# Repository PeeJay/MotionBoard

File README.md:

# MotionBoard
FirePick Delta/Ramps compatible motion controller running Smoothie

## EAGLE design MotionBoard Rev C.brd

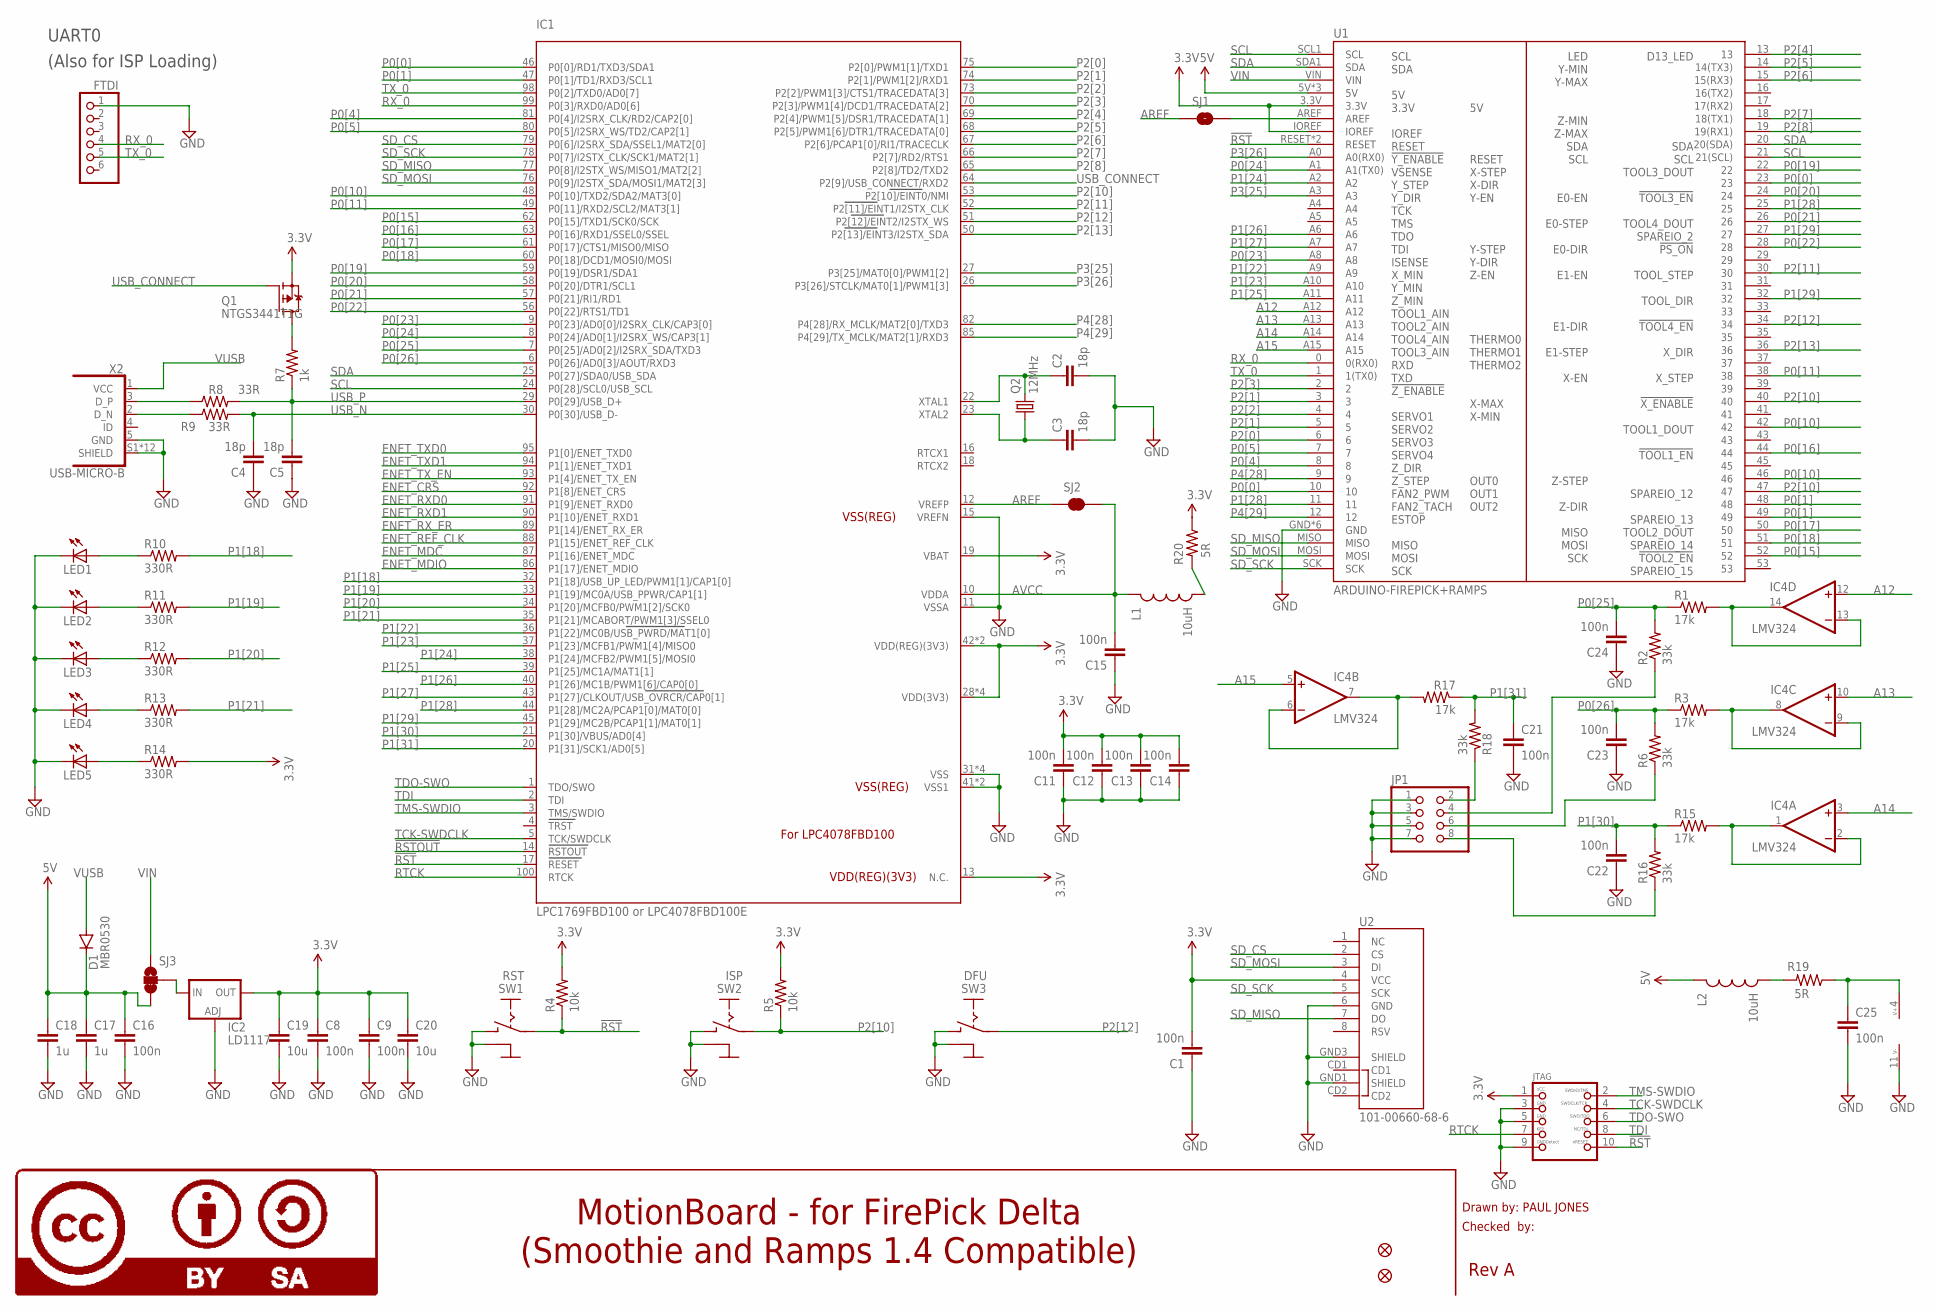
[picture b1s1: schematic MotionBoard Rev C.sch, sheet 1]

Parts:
C1, C8, C9, C11, C12, C13, C14, C15, C16, C21, C22, C23, C24, C25: 100n; 0603
C2, C3, C4, C5: 18p; 0603
C17, C18: 1u; 0603
C19, C20: 10u; 0603
D1: MBR0530; SOD-123
DFU: SW3; TOGGLE-SW-SMD
FID5, FID6: FIDUCIAL1X2; FIDUCIAL-1X2
FTDI: PINHD-1X6; 1X06
IC1: LPC1769FBD100 or LPC4078FBD100E; LQFP100
IC2: LD1117; SOT223
IC4: LMV324; SO14
ISP: SW2; TOGGLE-SW-SMD
JP1: PINHD-2X04_2.54-SMD; 2X04SMD
JTAG: JTAG-CORTEXM3; 2X05_1.27MM_SMT
L1, L2: 10uH; 0603
LED1, LED2, LED3, LED4, LED5: LED; LED-1206-BOTTOM
LOGO6: LOGO-CC-BY-SAMEDIUM; LOGO-CC-BY-SA-MEDIUM
Q1: NTGS3441T1G; SC74_INFINEON
Q2: 12MHz; HC49UP
R1, R3, R15, R17: 17k; 0603
R2, R6, R16, R18: 33k; 0603
R4, R5: 10k; R0603
R7: 1k; R0603
R8, R9: 33R; R0603
R10, R11, R12, R13, R14: 330R; R0603
R19, R20: 5R; 0603
RST: SW1; TOGGLE-SW-SMD
SJ1: JUMPER-PAD-2-NOYES_SILK; PAD-JUMPER-2-NO_YES_SILK
SJ2: JUMPER-PAD-2-NC_BY_TRACE; PAD-JUMPER-2-NC_BY_TRACE_YES_SILK
SJ3: JUMPER-PAD-3-2OF3_NC_BY_TRACE_SMALL; PAD-JUMPER-3-2OF3_NC_BY_TRACE_YES_SILK_FULL_BOX
U1: ARDUINO-FIREPICK+RAMPS; ARDUINO_MEGA_NEW
U2: 101-00660-68-6; MICRO-SD-SOCKET-PP
X2: USB-MICRO-B; FCI-10118194-0001LF

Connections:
3.3V: C1.2, C8.1, C9.1, C11.2, C12.2, C13.2, C14.2, C19.1, C20.1, IC1.13 (N.C.), IC1.19 (VBAT), IC1.28 (VDD(3V3)), IC1.42 (VDD(REG)(3V3)), IC1.54 (VDD(3V3)), IC1.71 (VDD(3V3)), IC1.84 (VDD(REG)(3V3)), IC1.96 (VDD(3V3)), IC2.4 (OUT), JTAG.1, Q1.4 (S), R4.2, R5.2, R14.2, R20.1, U1.3.3V, U1.IOREF, U2.4 (VCC); also elsewhere on the board
5V: C16.1, C17.1, C18.1, D1.C, L2.1, SJ3.3, U1.5V, U1.5V@1 (5V), U1.5V@2 (5V)
!RST: IC1.17 (RESET), JTAG.10, R4.1, RST.3 (I), RST.4 (I), U1.RESET, U1.RST (RESET)
!RSTOUT: IC1.14 (RSTOUT); also elsewhere on the board
A12: IC4.12 (+IN), U1.A12
A13: IC4.10 (+IN), U1.A13
A14: IC4.3 (+IN), U1.A14
A15: IC4.5 (+IN), U1.A15
AREF: IC1.12 (VREFP), SJ1.1, SJ2.1
AVCC: C15.2, IC1.10 (VDDA), L1.1, SJ2.2
D_N: R9.1, X2.2 (D_N)
D_P: R8.1, X2.3 (D_P)
ENET_CRS: IC1.92 (P1[8]/ENET_CRS); also elsewhere on the board
ENET_MDC: IC1.87 (P1[16]/ENET_MDC); also elsewhere on the board
ENET_MDIO: IC1.86 (P1[17]/ENET_MDIO); also elsewhere on the board
ENET_REF_CLK: IC1.88 (P1[15]/ENET_REF_CLK); also elsewhere on the board
ENET_RXD0: IC1.91 (P1[9]/ENET_RXD0); also elsewhere on the board
ENET_RXD1: IC1.90 (P1[10]/ENET_RXD1); also elsewhere on the board
ENET_RX_ER: IC1.89 (P1[14]/ENET_RX_ER); also elsewhere on the board
ENET_TXD0: IC1.95 (P1[0]/ENET_TXD0); also elsewhere on the board
ENET_TXD1: IC1.94 (P1[1]/ENET_TXD1); also elsewhere on the board
ENET_TX_EN: IC1.93 (P1[4]/ENET_TX_EN); also elsewhere on the board
GND: C1.1, C2.2, C3.2, C4.1, C5.1, C8.2, C9.2, C11.1, C12.1, C13.1, C14.1, C15.1, C16.2, C17.2, C18.2, C19.2, C20.2, C21.2, C22.1, C23.1, C24.1, C25.2, DFU.1 (C), DFU.2 (C), DFU.GND, FTDI.1, IC1.11 (VSSA), IC1.15 (VREFN), IC1.31 (VSS), IC1.41 (VSS1), IC1.55 (VSS), IC1.72 (VSS), IC1.83 (VSS1), IC1.97 (VSS), IC2.1 (ADJ), IC4.11 (V-), ISP.1 (C), ISP.2 (C), ISP.GND, JP1.1, JP1.3, JP1.5, JP1.7, JTAG.3, JTAG.5, JTAG.9, LED1.C, LED2.C, LED3.C, LED4.C, LED5.C, RST.1 (C), RST.2 (C), RST.GND, U1.GND, U1.GND@0 (GND), U1.GND@1 (GND), U1.GND@2 (GND), U1.GND@3 (GND), U1.GNDI (GND), U2.6 (GND), U2.GND1 (SHIELD), U2.GND3 (SHIELD), X2.5 (GND), X2.S1 (SHIELD), X2.S2 (SHIELD), X2.S3 (SHIELD), X2.S4 (SHIELD), X2.S5 (SHIELD), X2.S6 (SHIELD), X2.S7 (SHIELD), X2.S8 (SHIELD), X2.S9 (SHIELD), X2.S10 (SHIELD), X2.S11 (SHIELD), X2.S12 (SHIELD); also elsewhere on the board
unnamed: C2.1, IC1.22 (XTAL1), Q2.2
unnamed: C3.1, IC1.23 (XTAL2), Q2.1
unnamed: SJ1.2, U1.AREF
unnamed: IC4.6 (-IN), IC4.7 (OUT), R17.2
unnamed: IC2.3 (IN), SJ3.2
unnamed: JP1.2, R18.1
unnamed: IC4.13 (-IN), IC4.14 (OUT), R1.2
unnamed: JP1.8, R16.1
unnamed: IC4.8 (OUT), IC4.9 (-IN), R3.2
unnamed: JP1.6, R6.1
unnamed: IC4.1 (OUT), IC4.2 (-IN), R15.2
unnamed: JP1.4, R2.1
unnamed: C25.1, IC4.4 (V+), R19.1
unnamed: L2.2, R19.2
unnamed: L1.2, R20.2
unnamed: Q1.1 (D), Q1.2 (D), Q1.5 (D), Q1.6 (D), R7.2
unnamed: LED5.A, R14.1
unnamed: LED4.A, R13.1
unnamed: LED3.A, R12.1
unnamed: LED2.A, R11.1
unnamed: LED1.A, R10.1
P0[0]: IC1.46 (P0[0]/RD1/TXD3/SDA1), U1.10, U1.23
P0[1]: IC1.47 (P0[1]/TD1/RXD3/SCL1), U1.48, U1.49
P0[4]: IC1.81 (P0[4]/I2SRX_CLK/RD2/CAP2[0]), U1.8
P0[5]: IC1.80 (P0[5]/I2SRX_WS/TD2/CAP2[1]), U1.7
P0[10]: IC1.48 (P0[10]/TXD2/SDA2/MAT3[0]), U1.42, U1.46
P0[11]: IC1.49 (P0[11]/RXD2/SCL2/MAT3[1]), U1.38
P0[15]: IC1.62 (P0[15]/TXD1/SCK0/SCK), U1.52
P0[16]: IC1.63 (P0[16]/RXD1/SSEL0/SSEL), U1.44
P0[17]: IC1.61 (P0[17]/CTS1/MISO0/MISO), U1.50
P0[18]: IC1.60 (P0[18]/DCD1/MOSI0/MOSI), U1.51
P0[19]: IC1.59 (P0[19]/DSR1/SDA1), U1.22
P0[20]: IC1.58 (P0[20]/DTR1/SCL1), U1.24
P0[21]: IC1.57 (P0[21]/RI1/RD1), U1.26
P0[22]: IC1.56 (P0[22]/RTS1/TD1), U1.28
P0[23]: IC1.9 (P0[23]/AD0[0]/I2SRX_CLK/CAP3[0]), U1.A8
P0[24]: IC1.8 (P0[24]/AD0[1]/I2SRX_WS/CAP3[1]), U1.A1 (A1(TX0))
P0[25]: C24.2, IC1.7 (P0[25]/AD0[2]/I2SRX_SDA/TXD3), R1.1, R2.2
P0[26]: C23.2, IC1.6 (P0[26]/AD0[3]/AOUT/RXD3), R3.1, R6.2
P1[18]: IC1.32 (P1[18]/USB_UP_LED/PWM1[1]/CAP1[0]), R10.2
P1[19]: IC1.33 (P1[19]/MC0A/USB_PPWR/CAP1[1]), R11.2
P1[20]: IC1.34 (P1[20]/MCFB0/PWM1[2]/SCK0), R12.2
P1[21]: IC1.35 (P1[21]/MCABORT/PWM1[3]/SSEL0), R13.2
P1[22]: IC1.36 (P1[22]/MC0B/USB_PWRD/MAT1[0]), U1.A9
P1[23]: IC1.37 (P1[23]/MCFB1/PWM1[4]/MISO0), U1.A10
P1[24]: IC1.38 (P1[24]/MCFB2/PWM1[5]/MOSI0), U1.A2
P1[25]: IC1.39 (P1[25]/MC1A/MAT1[1]), U1.A11
P1[26]: IC1.40 (P1[26]/MC1B/PWM1[6]/CAP0[0]), U1.A6
P1[27]: IC1.43 (P1[27]/CLKOUT/USB_OVRCR/CAP0[1]), U1.A7
P1[28]: IC1.44 (P1[28]/MC2A/PCAP1[0]/MAT0[0]), U1.11, U1.25
P1[29]: IC1.45 (P1[29]/MC2B/PCAP1[1]/MAT0[1]), U1.27, U1.32
P1[30]: C22.2, IC1.21 (P1[30]/VBUS/AD0[4]), R15.1, R16.2
P1[31]: C21.1, IC1.20 (P1[31]/SCK1/AD0[5]), R17.1, R18.2
P2[0]: IC1.75 (P2[0]/PWM1[1]/TXD1), U1.6
P2[1]: IC1.74 (P2[1]/PWM1[2]/RXD1), U1.3, U1.5
P2[2]: IC1.73 (P2[2]/PWM1[3]/CTS1/TRACEDATA[3]), U1.4
P2[3]: IC1.70 (P2[3]/PWM1[4]/DCD1/TRACEDATA[2]), U1.2
P2[4]: IC1.69 (P2[4]/PWM1[5]/DSR1/TRACEDATA[1]), U1.13
P2[5]: IC1.68 (P2[5]/PWM1[6]/DTR1/TRACEDATA[0]), U1.14 (14(TX3))
P2[6]: IC1.67 (P2[6]/PCAP1[0]/RI1/TRACECLK), U1.15 (15(RX3))
P2[7]: IC1.66 (P2[7]/RD2/RTS1), U1.18 (18(TX1))
P2[8]: IC1.65 (P2[8]/TD2/TXD2), U1.19 (19(RX1))
P2[10]: IC1.53 (P2[10]/EINT0/NMI), ISP.3 (I), ISP.4 (I), R5.1, U1.40, U1.47
P2[11]: IC1.52 (P2[11]/EINT1/I2STX_CLK), U1.30
P2[12]: DFU.3 (I), DFU.4 (I), IC1.51 (P2[12]/EINT2/I2STX_WS), U1.34
P2[13]: IC1.50 (P2[13]/EINT3/I2STX_SDA), U1.36
P3[25]: IC1.27 (P3[25]/MAT0[0]/PWM1[2]), U1.A3
P3[26]: IC1.26 (P3[26]/STCLK/MAT0[1]/PWM1[3]), U1.A0 (A0(RX0))
P4[28]: IC1.82 (P4[28]/RX_MCLK/MAT2[0]/TXD3), U1.9
P4[29]: IC1.85 (P4[29]/TX_MCLK/MAT2[1]/RXD3), U1.12
RTCK: IC1.100 (RTCK), JTAG.7
RX_0: FTDI.4, IC1.99 (P0[3]/RXD0/AD0[6]), U1.0 (0(RX0))
SCL: IC1.24 (P0[28]/SCL0/USB_SCL), U1.21 (21(SCL)), U1.SCL1 (SCL)
SDA: IC1.25 (P0[27]/SDA0/USB_SDA), U1.20 (20(SDA)), U1.SDA1 (SDA)
SD_CS: IC1.79 (P0[6]/I2SRX_SDA/SSEL1/MAT2[0]), U2.2 (CS)
SD_MISO: IC1.77 (P0[8]/I2STX_WS/MISO1/MAT2[2]), U1.MISO, U2.7 (DO)
SD_MOSI: IC1.76 (P0[9]/I2STX_SDA/MOSI1/MAT2[3]), U1.MOSI, U2.3 (DI)
SD_SCK: IC1.78 (P0[7]/I2STX_CLK/SCK1/MAT2[1]), U1.SCK, U2.5 (SCK)
TCK-SWDCLK: IC1.5 (TCK/SWDCLK), JTAG.4
TDI: IC1.2 (TDI), JTAG.8
TDO-SWO: IC1.1 (TDO/SWO), JTAG.6
TMS-SWDIO: IC1.3 (TMS/SWDIO), JTAG.2
TX_0: FTDI.5, IC1.98 (P0[2]/TXD0/AD0[7]), U1.1 (1(TX0))
USB_CONNECT: IC1.64 (P2[9]/USB_CONNECT/RXD2), Q1.3 (G)
USB_N: C4.2, IC1.30 (P0[30]/USB_D-), R9.2
USB_P: C5.2, IC1.29 (P0[29]/USB_D+), R7.1, R8.2
VIN: SJ3.1, U1.VIN
VUSB: D1.A, X2.1 (VCC)

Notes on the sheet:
Drawn by: PAUL JONES
Checked by:
Rev A
MotionBoard - for FirePick Delta (Smoothie and Ramps 1.4 Compatible)
UART0
(Also for ISP Loading)

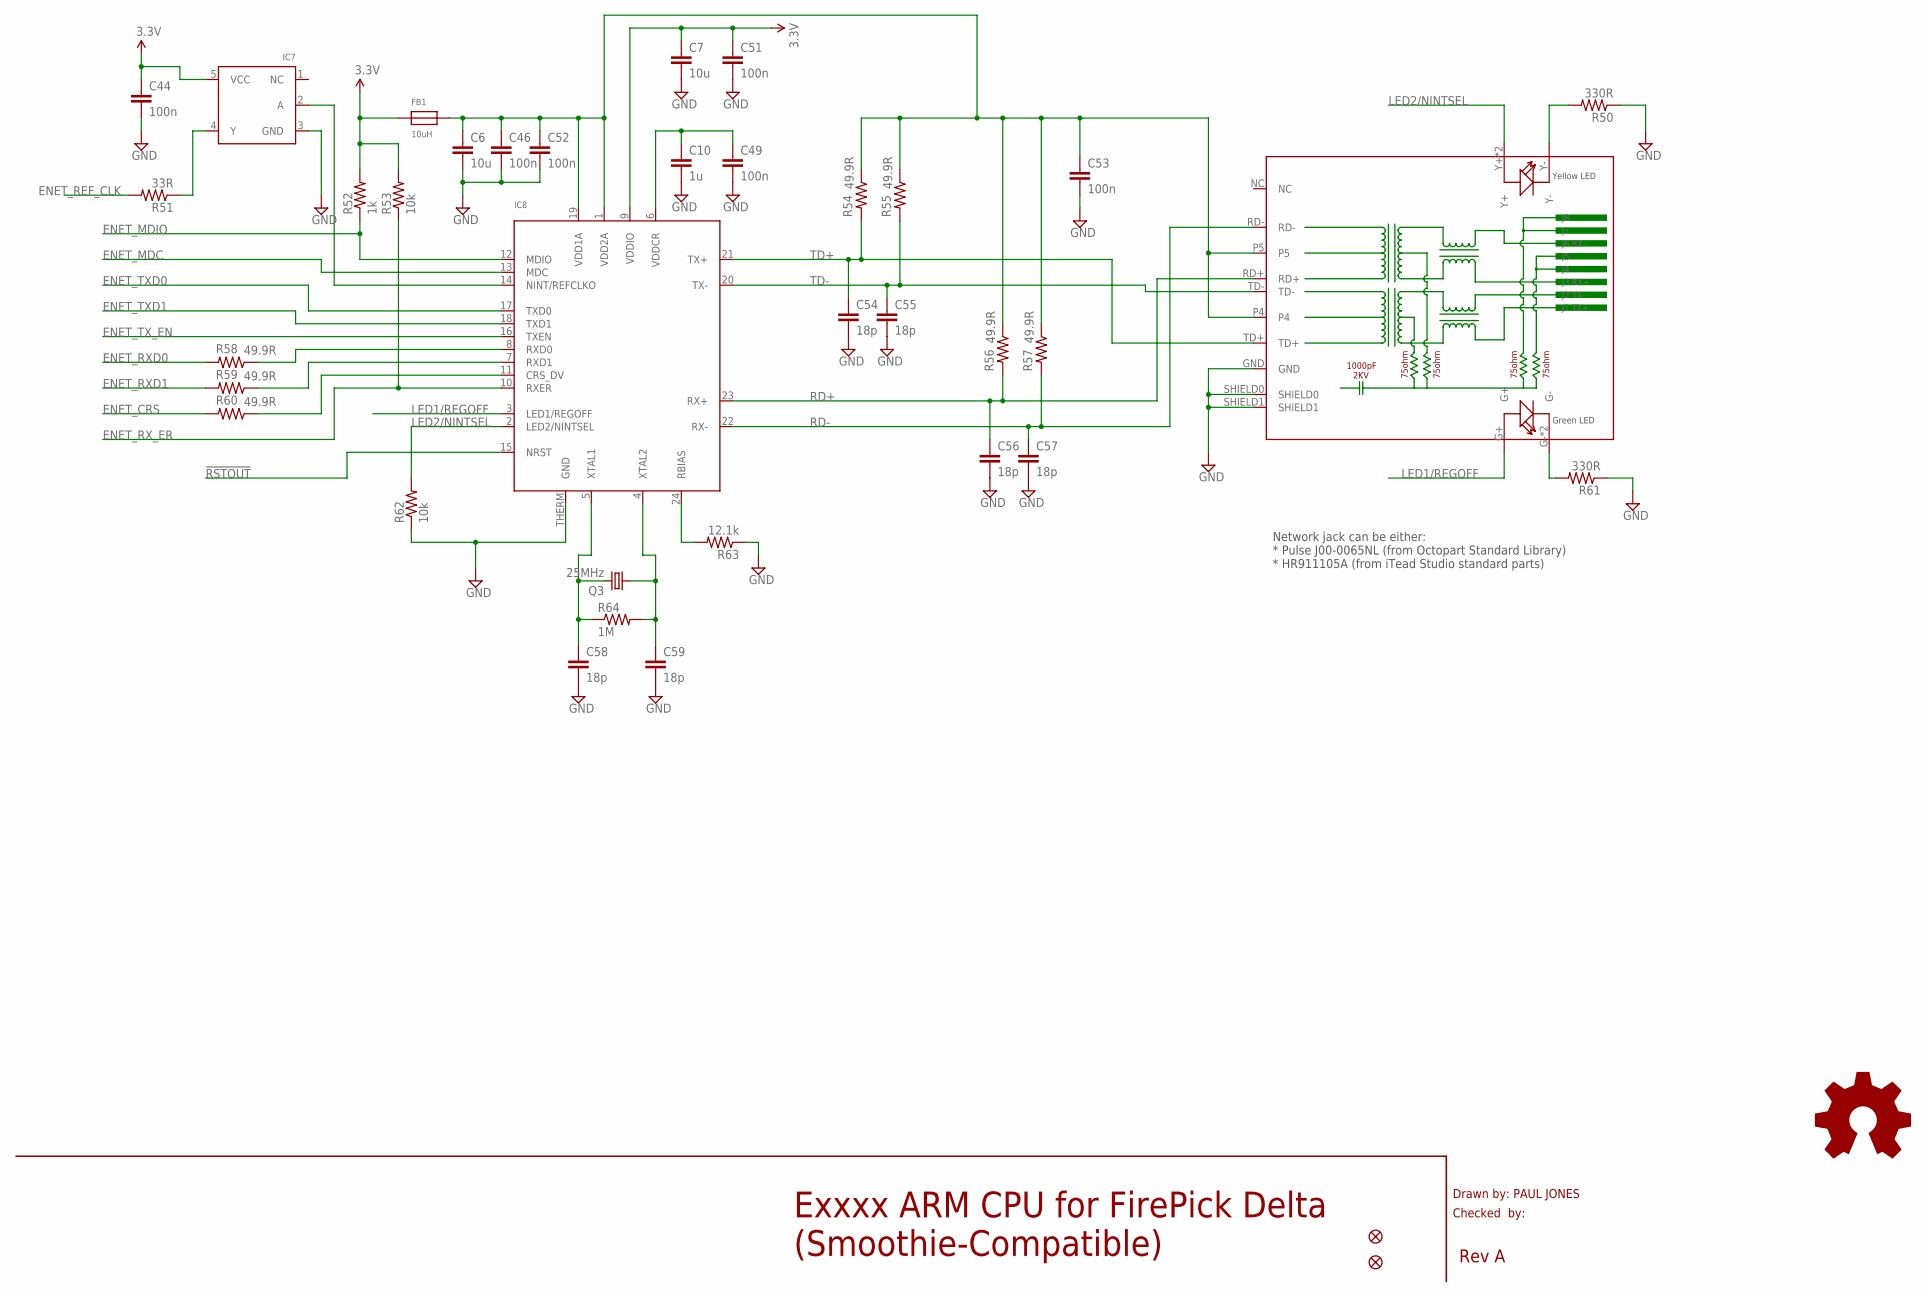
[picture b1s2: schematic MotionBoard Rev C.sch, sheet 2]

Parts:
C6, C7: 10u; 0603
C10: 1u; 0603
C44, C46, C49, C51, C52, C53: 100n; 0603
C54, C55, C56, C57, C58, C59: 18p; 0603
FB1: 10uH; 0603
FID17, FID18: FIDUCIAL1X2; FIDUCIAL-1X2
IC7: 74LVC1G04; SOT23-5
IC8: LAN8720; QFN24_4MM
LOGO10: LOGO-OSHWSMALL; LOGO-OSHW-SMALL
Q3: 25MHz; HC49UP
R50, R61: 330R; R0603
R51: 33R; R0603
R52: 1k; R0603
R53, R62: 10k; R0603
R54, R55, R56, R57, R58, R59, R60: 49.9R; R0603
R63: 12.1k; R0603
R64: 1M; R0603
RJ1: HR911105A

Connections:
3.3V: C7.1, C44.1, C51.1, FB1.1, IC7.5 (VCC), IC8.9 (VDDIO), R52.2, R53.2; also elsewhere on the board
!RSTOUT: IC8.15 (NRST); also elsewhere on the board
ENET_CRS: R60.2; also elsewhere on the board
ENET_MDC: IC8.13 (MDC); also elsewhere on the board
ENET_MDIO: IC8.12 (MDIO), R52.1; also elsewhere on the board
ENET_REF_CLK: R51.2; also elsewhere on the board
ENET_RXD0: R58.2; also elsewhere on the board
ENET_RXD1: R59.2; also elsewhere on the board
ENET_RX_ER: IC8.10 (RXER), R53.1; also elsewhere on the board
ENET_TXD0: IC8.17 (TXD0); also elsewhere on the board
ENET_TXD1: IC8.18 (TXD1); also elsewhere on the board
ENET_TX_EN: IC8.16 (TXEN); also elsewhere on the board
GND: C6.2, C7.2, C10.2, C44.2, C46.2, C49.2, C51.2, C52.2, C53.2, C54.2, C55.2, C56.2, C57.2, C58.2, C59.2, IC7.3 (GND), IC8.THERM (GND), R50.1, R61.1, R62.1, R63.1, RJ1.GND, RJ1.SHIELD0, RJ1.SHIELD1; also elsewhere on the board
LED1/REGOFF: IC8.3 (LED1/REGOFF), RJ1.G+
LED2/NINTSEL: IC8.2 (LED2/NINTSEL), R62.2, RJ1.Y+, RJ1.Y++ (Y+)
unnamed: IC8.11 (CRS_DV), R60.1
unnamed: IC8.24 (RBIAS), R63.2
unnamed: C10.1, C49.1, IC8.6 (VDDCR)
unnamed: IC7.2 (A), IC8.14 (NINT/REFCLKO)
unnamed: R61.2, RJ1.G-, RJ1.G-- (G-)
unnamed: IC8.8 (RXD0), R58.1
unnamed: R50.2, RJ1.Y-
unnamed: IC8.7 (RXD1), R59.1
unnamed: C59.1, IC8.4 (XTAL2), Q3.1, R64.2
unnamed: C58.1, IC8.5 (XTAL1), Q3.2, R64.1
unnamed: IC7.4 (Y), R51.1
RD+: C56.1, IC8.23 (RX+), R56.2, RJ1.RD+
RD-: C57.1, IC8.22 (RX-), R57.2, RJ1.RD-
TD+: C54.1, IC8.21 (TX+), R54.2, RJ1.TD+
TD-: C55.1, IC8.20 (TX-), R55.2, RJ1.TD-
VDD: C6.1, C46.1, C52.1, C53.1, FB1.2, IC8.1 (VDD2A), IC8.19 (VDD1A), R54.1, R55.1, R56.1, R57.1, RJ1.P4, RJ1.P5

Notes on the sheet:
Drawn by: PAUL JONES
Checked by:
Rev A
Exxxx ARM CPU for FirePick Delta (Smoothie-Compatible)
Network jack can be either: * Pulse J00‑0065NL (from Octopart Standard Library) * HR911105A (from iTead Studio standard parts)

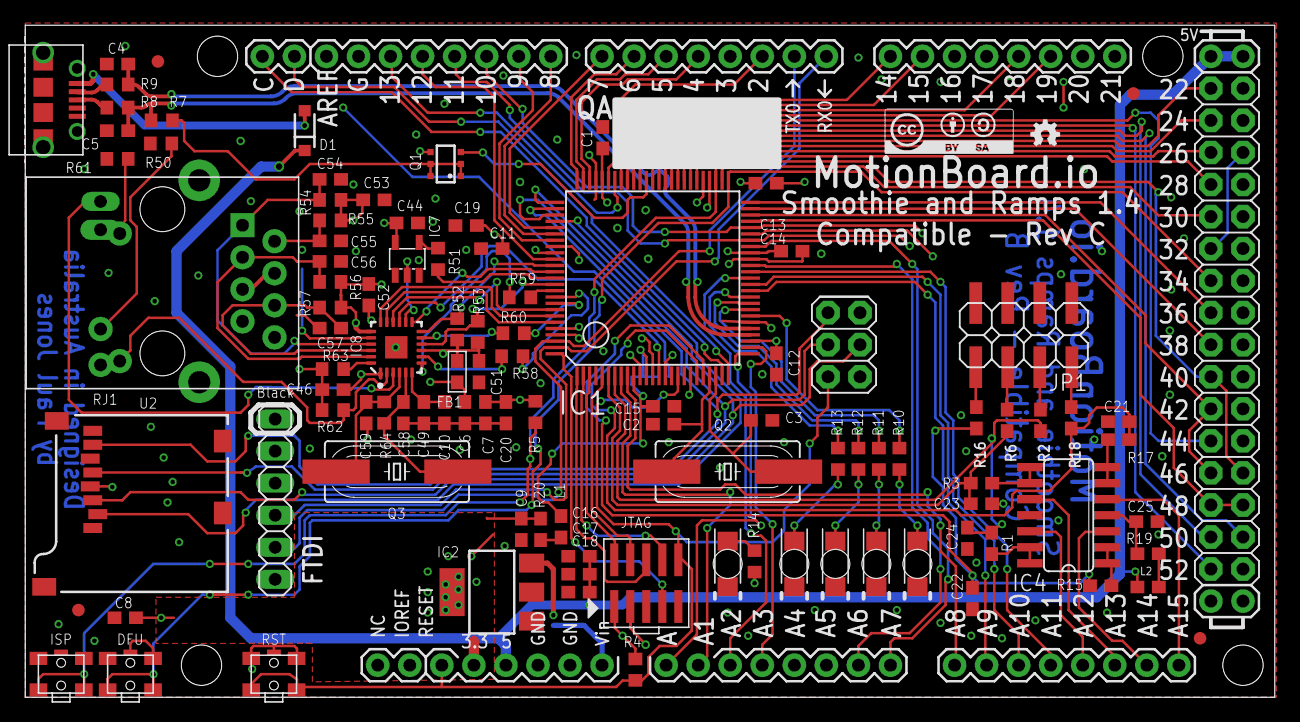
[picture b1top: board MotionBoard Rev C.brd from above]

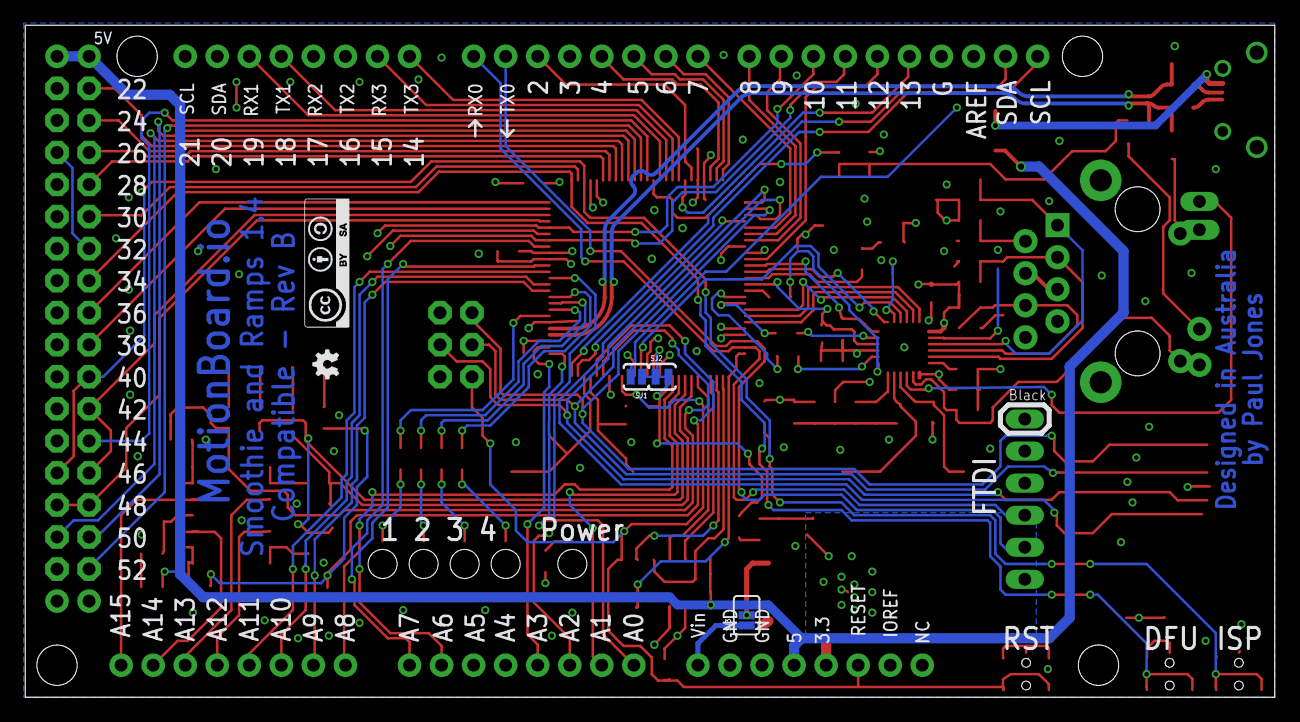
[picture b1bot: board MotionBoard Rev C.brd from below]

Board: 4 copper layers, 99.0 x 53.3 mm, 110 parts (5 on the bottom side), 129 nets.

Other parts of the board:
LOGO2: LOGO-OSHWSMALL; LOGO-OSHW-SMALL
LOGO3: LOGO-CC-BY-SAMEDIUM; LOGO-CC-BY-SA-MEDIUM

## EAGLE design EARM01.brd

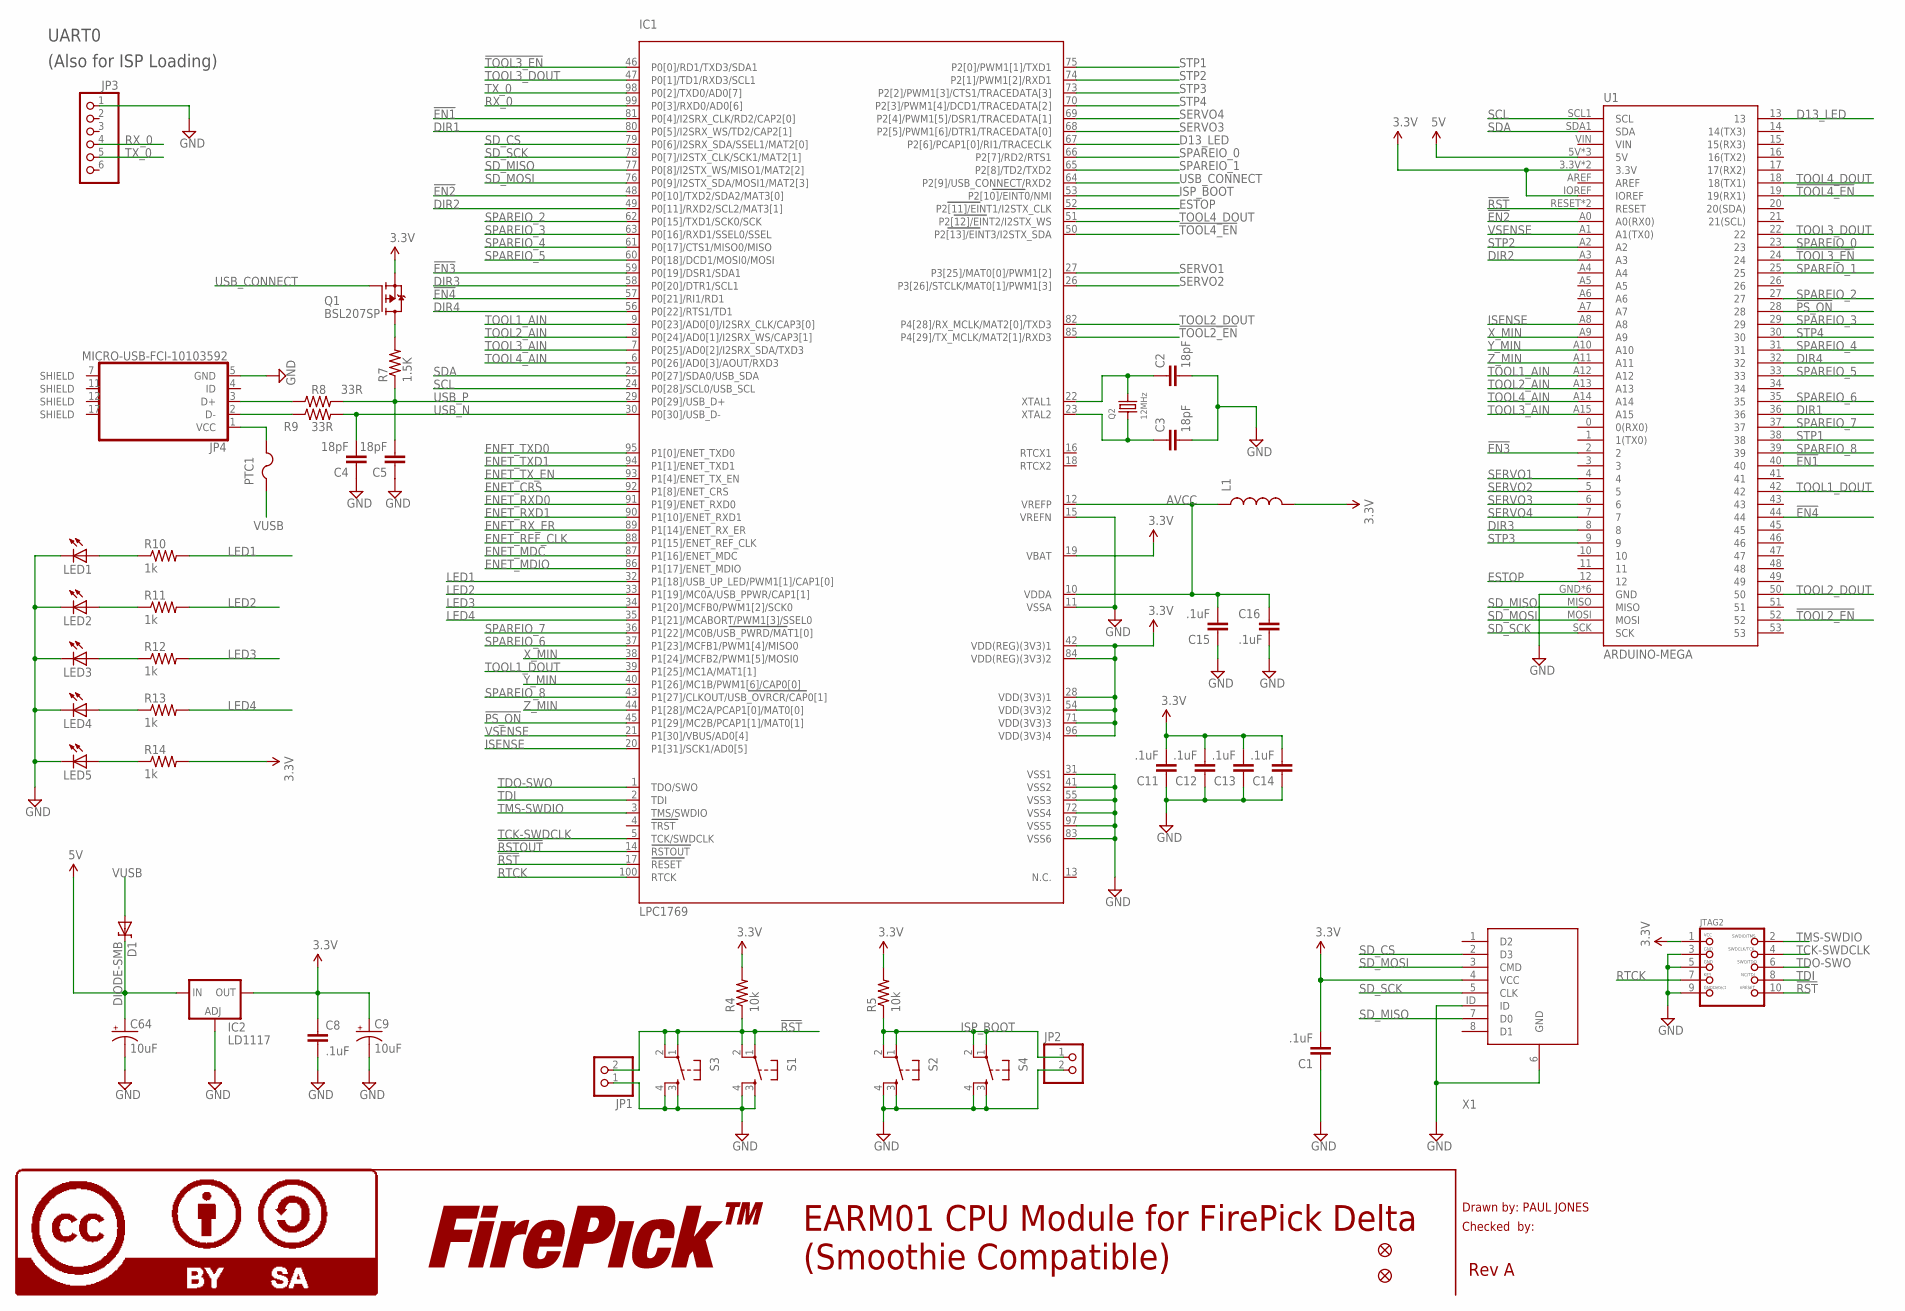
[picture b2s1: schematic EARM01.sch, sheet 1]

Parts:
C1, C8, C11, C12, C13, C14, C15, C16: .1uF; C0603
C2, C3, C4, C5: 18pF; C0603
C9, C64: 10uF; EIA3216
D1: DIODE-SMB; SMB-DIODE
FID5, FID6: FIDUCIAL1X2; FIDUCIAL-1X2
IC1: LPC1769; LQFP100
IC2: LD1117; SOT223
JP1, JP2: PINHD-1X2; 1X02
JP3: PINHD-1X6; 1X06
JP4: MICRO-USB-FCI-10103592
JTAG2: JTAG-CORTEXM3; 2X05_1.27MM_SMT
L1: INDUCTOR0603; 0603
LED1, LED2, LED3, LED4, LED5: LED; LED-1206-BOTTOM
LOGO4: LOGO-FIREPICKMEDIUM; LOGO-FIREPICK-MEDIUM
LOGO6: LOGO-CC-BY-SAMEDIUM; LOGO-CC-BY-SA-MEDIUM
PTC1: PTCFUSE-1812; 1812
Q1: BSL207SP; SC74_INFINEON
Q2: 12MHz; CRYSTAL_3.2X2.5
R4, R5: 10k; R0603
R7: 1.5K; R0603
R8, R9: 33R; R0603
R10, R11, R12, R13, R14: 1k; R0603
S1, S2, S3, S4: TAC_SWITCHSMD; TACTILE_SWITCH_SMD
U1: ARDUINO-MEGA; ARDUINO_MEGA_NEW
X1: ST9S008V4AR1500

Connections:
3.3V: C1.2, C8.1, C9.A (+), C11.2, C12.2, C13.2, C14.2, IC1.19 (VBAT), IC1.28 (VDD(3V3)1), IC1.42 (VDD(REG)(3V3)1), IC1.54 (VDD(3V3)2), IC1.71 (VDD(3V3)3), IC1.84 (VDD(REG)(3V3)2), IC1.96 (VDD(3V3)4), IC2.4 (OUT), JTAG2.1, L1.2, Q1.4 (S), R4.2, R5.2, R14.2, U1.3.3V, U1.IOREF, U1.VCC (3.3V), X1.4 (VCC); also elsewhere on the board
5V: C64.A (+), D1.C, IC2.3 (IN), U1.5V, U1.5V@1 (5V), U1.5V@2 (5V)
!EN1: IC1.81 (P0[4]/I2SRX_CLK/RD2/CAP2[0]), U1.40
!EN2: IC1.48 (P0[10]/TXD2/SDA2/MAT3[0]), U1.A0 (A0(RX0))
!EN3: IC1.59 (P0[19]/DSR1/SDA1), U1.2
!EN4: IC1.57 (P0[21]/RI1/RD1), U1.44
!PS_ON: IC1.45 (P1[29]/MC2B/PCAP1[1]/MAT0[1]), U1.28
!RST: IC1.17 (RESET), JP1.2, JTAG2.10, R4.1, S1.1, S1.2, S3.1, S3.2, U1.RESET, U1.RST (RESET)
!RSTOUT: IC1.14 (RSTOUT); also elsewhere on the board
!TOOL2_EN: IC1.85 (P4[29]/TX_MCLK/MAT2[1]/RXD3), U1.52
!TOOL3_EN: IC1.46 (P0[0]/RD1/TXD3/SDA1), U1.24
!TOOL4_EN: IC1.50 (P2[13]/EINT3/I2STX_SDA), U1.19 (19(RX1))
AVCC: C15.2, C16.1, IC1.10 (VDDA), IC1.12 (VREFP), L1.1
D13_LED: IC1.67 (P2[6]/PCAP1[0]/RI1/TRACECLK), U1.13
DIR1: IC1.80 (P0[5]/I2SRX_WS/TD2/CAP2[1]), U1.36
DIR2: IC1.49 (P0[11]/RXD2/SCL2/MAT3[1]), U1.A3
DIR3: IC1.58 (P0[20]/DTR1/SCL1), U1.8
DIR4: IC1.56 (P0[22]/RTS1/TD1), U1.32
ENET_CRS: IC1.92 (P1[8]/ENET_CRS); also elsewhere on the board
ENET_MDC: IC1.87 (P1[16]/ENET_MDC); also elsewhere on the board
ENET_MDIO: IC1.86 (P1[17]/ENET_MDIO); also elsewhere on the board
ENET_REF_CLK: IC1.88 (P1[15]/ENET_REF_CLK); also elsewhere on the board
ENET_RXD0: IC1.91 (P1[9]/ENET_RXD0); also elsewhere on the board
ENET_RXD1: IC1.90 (P1[10]/ENET_RXD1); also elsewhere on the board
ENET_RX_ER: IC1.89 (P1[14]/ENET_RX_ER); also elsewhere on the board
ENET_TXD0: IC1.95 (P1[0]/ENET_TXD0); also elsewhere on the board
ENET_TXD1: IC1.94 (P1[1]/ENET_TXD1); also elsewhere on the board
ENET_TX_EN: IC1.93 (P1[4]/ENET_TX_EN); also elsewhere on the board
ESTOP: IC1.52 (P2[11]/EINT1/I2STX_CLK), U1.12
GND: C1.1, C2.2, C3.2, C4.1, C5.1, C8.2, C9.C (-), C11.1, C12.1, C13.1, C14.1, C15.1, C16.2, C64.C (-), IC1.11 (VSSA), IC1.15 (VREFN), IC1.31 (VSS1), IC1.41 (VSS2), IC1.55 (VSS3), IC1.72 (VSS4), IC1.83 (VSS6), IC1.97 (VSS5), IC2.1 (ADJ), JP1.1, JP2.2, JP3.1, JP4.5 (GND), JTAG2.3, JTAG2.5, JTAG2.9, LED1.C, LED2.C, LED3.C, LED4.C, LED5.C, S1.3, S1.4, S2.3, S2.4, S3.3, S3.4, S4.3, S4.4, U1.GND, U1.GND@0 (GND), U1.GND@1 (GND), U1.GND@2 (GND), U1.GND@3 (GND), U1.GNDI (GND), X1.6 (GND), X1.ID; also elsewhere on the board
ISENSE: IC1.20 (P1[31]/SCK1/AD0[5]), U1.A8
ISP_BOOT: IC1.53 (P2[10]/EINT0/NMI), JP2.1, R5.1, S2.1, S2.2, S4.1, S4.2
LED1: IC1.32 (P1[18]/USB_UP_LED/PWM1[1]/CAP1[0]), R10.2
LED2: IC1.33 (P1[19]/MC0A/USB_PPWR/CAP1[1]), R11.2
LED3: IC1.34 (P1[20]/MCFB0/PWM1[2]/SCK0), R12.2
LED4: IC1.35 (P1[21]/MCABORT/PWM1[3]/SSEL0), R13.2
unnamed: C2.1, IC1.22 (XTAL1), Q2.2
unnamed: C3.1, IC1.23 (XTAL2), Q2.1
unnamed: JP4.1 (VCC), PTC1.2
unnamed: Q1.1 (D), Q1.2 (D), Q1.5 (D), Q1.6 (D), R7.2
unnamed: JP4.3 (D+), R8.1
unnamed: JP4.2 (D-), R9.1
unnamed: LED5.A, R14.1
unnamed: LED4.A, R13.1
unnamed: LED3.A, R12.1
unnamed: LED2.A, R11.1
unnamed: LED1.A, R10.1
RTCK: IC1.100 (RTCK), JTAG2.7
RX_0: IC1.99 (P0[3]/RXD0/AD0[6]), JP3.4
SCL: IC1.24 (P0[28]/SCL0/USB_SCL), U1.SCL1 (SCL)
SDA: IC1.25 (P0[27]/SDA0/USB_SDA), U1.SDA1 (SDA)
SD_CS: IC1.79 (P0[6]/I2SRX_SDA/SSEL1/MAT2[0]), X1.2 (D3)
SD_MISO: IC1.77 (P0[8]/I2STX_WS/MISO1/MAT2[2]), U1.MISO, X1.7 (D0)
SD_MOSI: IC1.76 (P0[9]/I2STX_SDA/MOSI1/MAT2[3]), U1.MOSI, X1.3 (CMD)
SD_SCK: IC1.78 (P0[7]/I2STX_CLK/SCK1/MAT2[1]), U1.SCK, X1.5 (CLK)
SERVO1: IC1.27 (P3[25]/MAT0[0]/PWM1[2]), U1.4
SERVO2: IC1.26 (P3[26]/STCLK/MAT0[1]/PWM1[3]), U1.5
SERVO3: IC1.68 (P2[5]/PWM1[6]/DTR1/TRACEDATA[0]), U1.6
SERVO4: IC1.69 (P2[4]/PWM1[5]/DSR1/TRACEDATA[1]), U1.7
SPAREIO_0: IC1.66 (P2[7]/RD2/RTS1), U1.23
SPAREIO_1: IC1.65 (P2[8]/TD2/TXD2), U1.25
SPAREIO_2: IC1.62 (P0[15]/TXD1/SCK0/SCK), U1.27
SPAREIO_3: IC1.63 (P0[16]/RXD1/SSEL0/SSEL), U1.29
SPAREIO_4: IC1.61 (P0[17]/CTS1/MISO0/MISO), U1.31
SPAREIO_5: IC1.60 (P0[18]/DCD1/MOSI0/MOSI), U1.33
SPAREIO_6: IC1.37 (P1[23]/MCFB1/PWM1[4]/MISO0), U1.35
SPAREIO_7: IC1.36 (P1[22]/MC0B/USB_PWRD/MAT1[0]), U1.37
SPAREIO_8: IC1.43 (P1[27]/CLKOUT/USB_OVRCR/CAP0[1]), U1.39
STP1: IC1.75 (P2[0]/PWM1[1]/TXD1), U1.38
STP2: IC1.74 (P2[1]/PWM1[2]/RXD1), U1.A2
STP3: IC1.73 (P2[2]/PWM1[3]/CTS1/TRACEDATA[3]), U1.9
STP4: IC1.70 (P2[3]/PWM1[4]/DCD1/TRACEDATA[2]), U1.30
TCK-SWDCLK: IC1.5 (TCK/SWDCLK), JTAG2.4
TDI: IC1.2 (TDI), JTAG2.8
TDO-SWO: IC1.1 (TDO/SWO), JTAG2.6
TMS-SWDIO: IC1.3 (TMS/SWDIO), JTAG2.2
TOOL1_AIN: IC1.9 (P0[23]/AD0[0]/I2SRX_CLK/CAP3[0]), U1.A12
TOOL1_DOUT: IC1.39 (P1[25]/MC1A/MAT1[1]), U1.42
TOOL2_AIN: IC1.8 (P0[24]/AD0[1]/I2SRX_WS/CAP3[1]), U1.A13
TOOL2_DOUT: IC1.82 (P4[28]/RX_MCLK/MAT2[0]/TXD3), U1.50
TOOL3_AIN: IC1.7 (P0[25]/AD0[2]/I2SRX_SDA/TXD3), U1.A15
TOOL3_DOUT: IC1.47 (P0[1]/TD1/RXD3/SCL1), U1.22
TOOL4_AIN: IC1.6 (P0[26]/AD0[3]/AOUT/RXD3), U1.A14
TOOL4_DOUT: IC1.51 (P2[12]/EINT2/I2STX_WS), U1.18 (18(TX1))
TX_0: IC1.98 (P0[2]/TXD0/AD0[7]), JP3.5
USB_CONNECT: IC1.64 (P2[9]/USB_CONNECT/RXD2), Q1.3 (G)
USB_N: C4.2, IC1.30 (P0[30]/USB_D-), R9.2
USB_P: C5.2, IC1.29 (P0[29]/USB_D+), R7.1, R8.2
VSENSE: IC1.21 (P1[30]/VBUS/AD0[4]), U1.A1 (A1(TX0))
VUSB: D1.A, PTC1.1
X_MIN: IC1.38 (P1[24]/MCFB2/PWM1[5]/MOSI0), U1.A9
Y_MIN: IC1.40 (P1[26]/MC1B/PWM1[6]/CAP0[0]), U1.A10
Z_MIN: IC1.44 (P1[28]/MC2A/PCAP1[0]/MAT0[0]), U1.A11

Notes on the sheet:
Drawn by: PAUL JONES
Checked by:
Rev A
EARM01 CPU Module for FirePick Delta (Smoothie Compatible)
UART0
(Also for ISP Loading)

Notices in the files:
parts and their libraries:
SparkFun-Aesthetics: Licensing: CC v3.0 Share-Alike You are welcome to use this library for commercial purposes.
SparkFun-DiscreteSemi: Licensing: Creative Commons ShareAlike 4.0 International - https://creativecommons.org/licenses/by-sa/4.0
